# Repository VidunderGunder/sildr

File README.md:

# Sildr

Everything Sildr and technical.

1.0 and 2.0 are legacy, and some relevant documentation can be found in `/legacy`. Keep in mind it's mostly in Norwegian.

## Order History

**Components:**  
https://no.mouser.com/OrderHistory/OrdersView.aspx  
Email: kristiankramas@outlook.com  
Username: `vidundergunder`  
Password: `******`

**PCB:**  
https://jlcpcb.com/order#EL  
Email: kristiankramas@outlook.com  
Username: `vidundergunder`  
Password: `******`

## Electrical System v3.0

### Overview Illustration (click on image to open Figma):

The system is split in two parts:

1. Base system
2. Optional data logging system (requires the base system)

### Base System

#### Simplified circuit diagram (click on image to run simulation):

> _Image may be outdated_
> 
> - Behavior can be controlled with an MCU, and has an analog fallback
> - Relay represents the solenoid valve
> - Voltmeter is a digital in pin, registering 0V as button presses
> - Logic sources are digital out pins
> - Resistor connected to pin 7 and 6 on the 555-timer can be changed out for a potentiometer to manually set timer on-site

#### Simulated Prototype Circuit (click on image to run simulation):

> _Image may be outdated_  
> 
> - Simulation requires an Autodesk account (you can use your google account)
> - Lightbulb represents the solenoid valve

#### Prototype Components

- 1x 555-timer
- 3x nMOS Transistor (MOSFET)  
(FQP30N06L 60V LOGIC N-Channel MOSFET)
- 3x 1k resistor
- 1x 4k7 resistor
- 1x 330 resistor
- 1x 1mF capacitor
- 1x Pushbutton
- 1x diode
- 12V DC power supply
- 5V DC power supply

#### Production Components

| Component      | Description                   | Image                                                    |
| -------------- | ----------------------------- | -------------------------------------------------------- |
| Button         | [Schurter Touchless Switch TTS](https://www.schurter.com/en/datasheet/TTS) |  |
| Solenoid Coil (Valve) | [Danfoss BE012DS Coil](https://store.danfoss.com/no/no/Climate-Solutions-for-cooling/Ventiler/Ventilspoler/Spoler-for-Magnetventiler/Magnetventilspole%2C-BE012DS%2C-Koblingsboks%2C-Multipakk/p/018F6756#/) |  |
| Transformer | [230VAC to 12VDC 2.0A (NB: Pick correct option)](https://www.biltema.no/en-no/construction/electrical-installations/lamp-sockets/led-transformer-12-v-dc-2000038013) |  |

### Data Logging System (optional)

_TODO_

| Component      | Description                   | Image                                                    |
| -------------- | ----------------------------- | -------------------------------------------------------- |
| Flowmeter | [Sensus HRI Pulsgiver](https://www.ahlsell.no/products/vvs-teknisk-produkter/ventiler---filter-og-instrumenter/vannmalere-med-tilbehor/4021402/) (1pulse/liter) [Datasheet](https://nobb-vavvs.no/API/Produktfiler/LastNed?id=27486&inline=) |  |

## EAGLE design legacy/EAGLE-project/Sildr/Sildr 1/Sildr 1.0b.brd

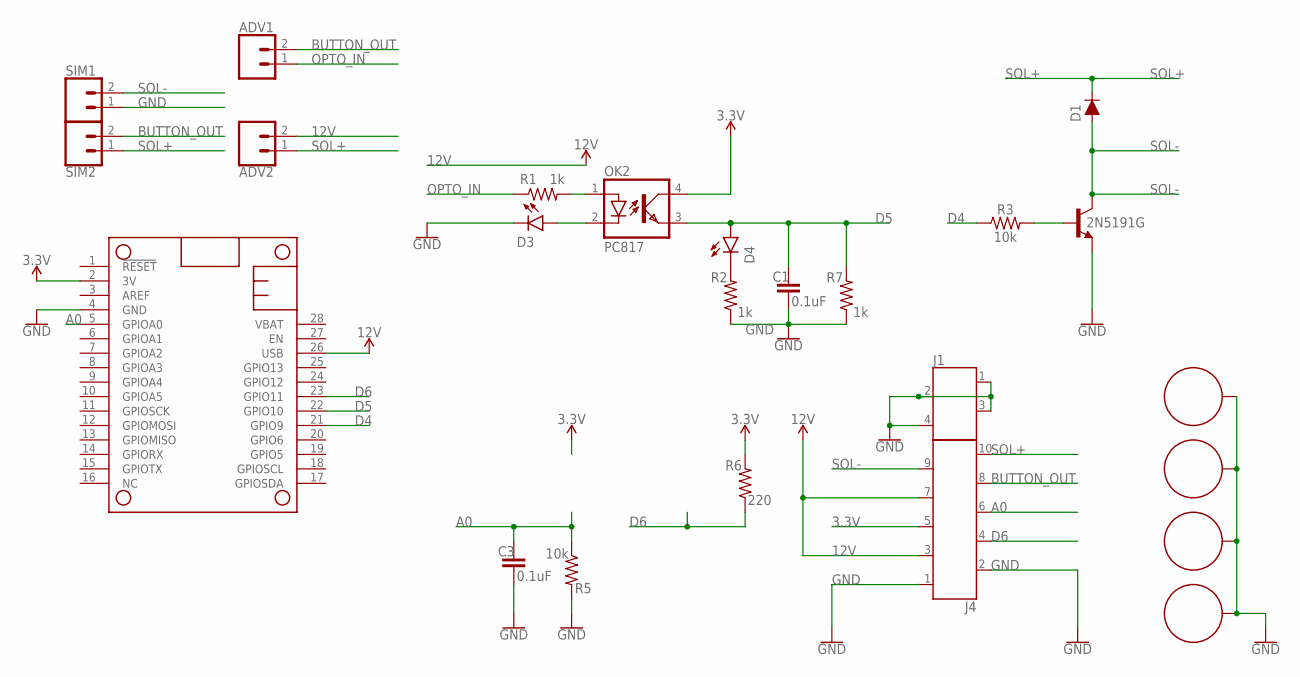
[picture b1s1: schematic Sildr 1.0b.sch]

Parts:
2N5191G: 2SC1944; T-30_V
ADV1, ADV2: CONN_02; 1X02
C1, C3: 0.1uF; CAP-PTH-SMALL-KIT
D1: 1A/50V/1.1V; DIODE-1N4001
D3, D4: LED3MM; LED_3MM
H1, H2, H3, H6: STANDOFF_ELECTRICAL; STANDOFF-ELECTRICAL
J1: 691412320004
J4: 691412320010
MS1: FEATHERWING_NODIM; FEATHERWING_DIM
OK2: PC817; DIL04
R1, R2, R7: 1k; AXIAL-0.3
R3, R5: 10k; AXIAL-0.3
R6: 220; AXIAL-0.3
SIM1, SIM2: CONN_02; 1X02

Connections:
3.3V: J4.5, MS1.2 (3V), OK2.4 (COL), R6.P$2 (2)
12V: ADV2.2, J4.3, J4.7, MS1.26 (USB)
A0: C3.1, J4.6, MS1.5 (GPIOA0), R5.P$1 (1)
BUTTON_OUT: ADV1.2, J4.8, SIM2.2
D4: MS1.21 (GPIO9), R3.P$1 (1)
D5: C1.1, D4.A, MS1.22 (GPIO10), OK2.3 (EMIT), R7.P$2 (2)
D6: J4.4, MS1.23 (GPIO11), R6.P$1 (1)
GND: 2N5191G.3 (E), C1.2, C3.2, D3.K (C), H1.P1, H2.P1, H3.P1, H6.P1, J1.1, J1.2, J1.3, J1.4, J4.1, J4.2, MS1.4 (GND), R2.P$1 (1), R5.P$2 (2), R7.P$1 (1), SIM1.1
unnamed: 2N5191G.1 (B), R3.P$2 (2)
unnamed: D3.A, OK2.2 (C)
unnamed: OK2.1 (A), R1.P$2 (2)
unnamed: D4.K (C), R2.P$2 (2)
OPTO_IN: ADV1.1, R1.P$1 (1)
SOL+: ADV2.1, D1.C, J4.10, SIM2.1
SOL-: 2N5191G.2 (C), D1.A, J4.9, SIM1.2

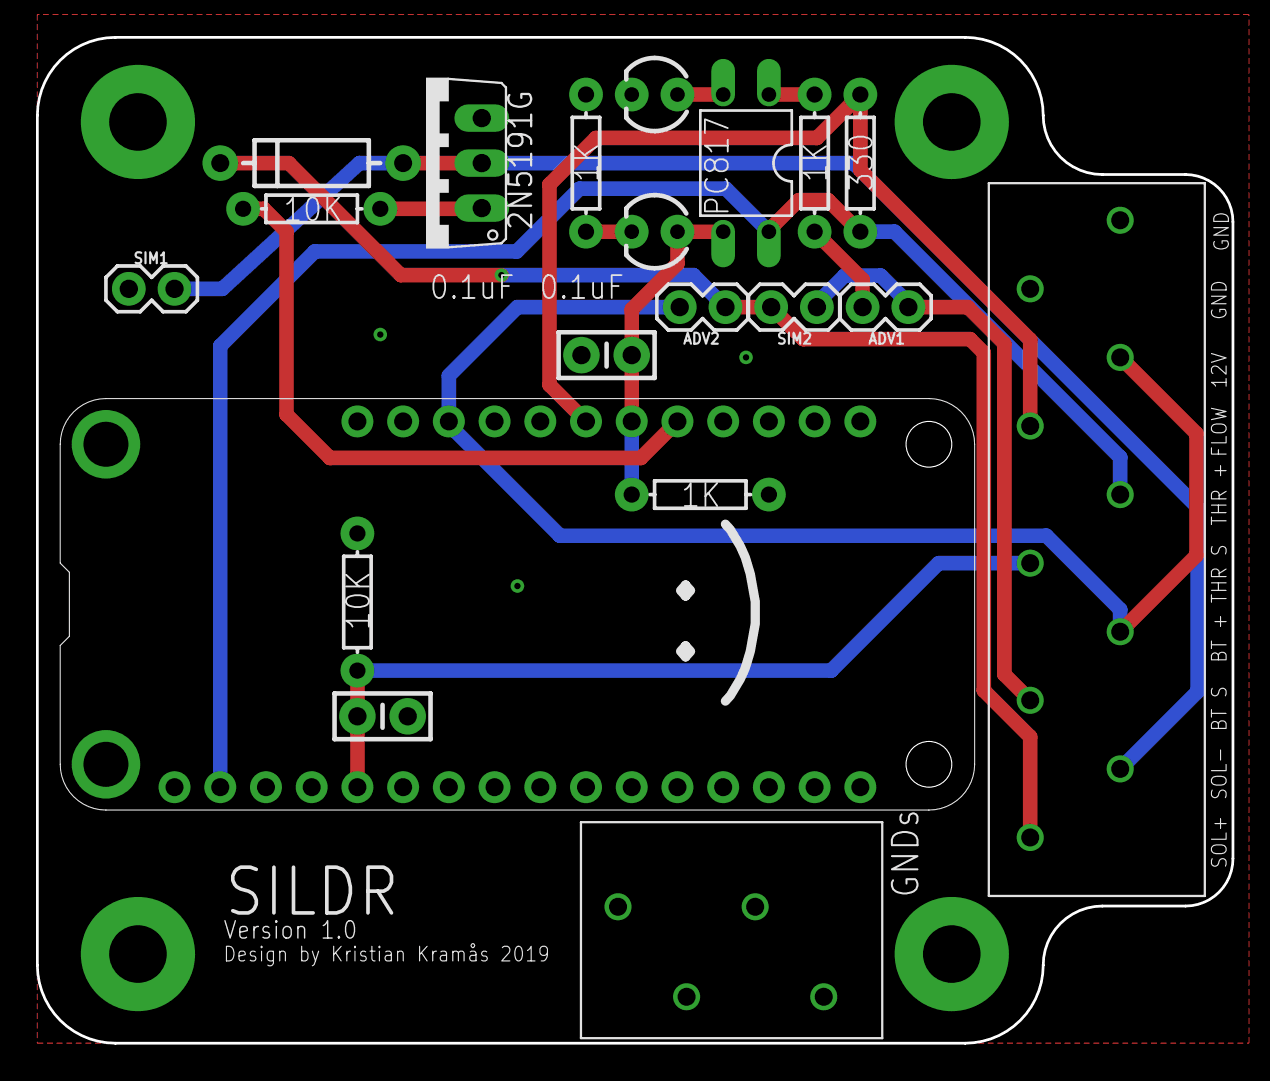
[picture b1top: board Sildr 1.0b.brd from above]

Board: 2 copper layers, 66.4 x 55.9 mm, 24 parts (0 on the bottom side), 15 nets.

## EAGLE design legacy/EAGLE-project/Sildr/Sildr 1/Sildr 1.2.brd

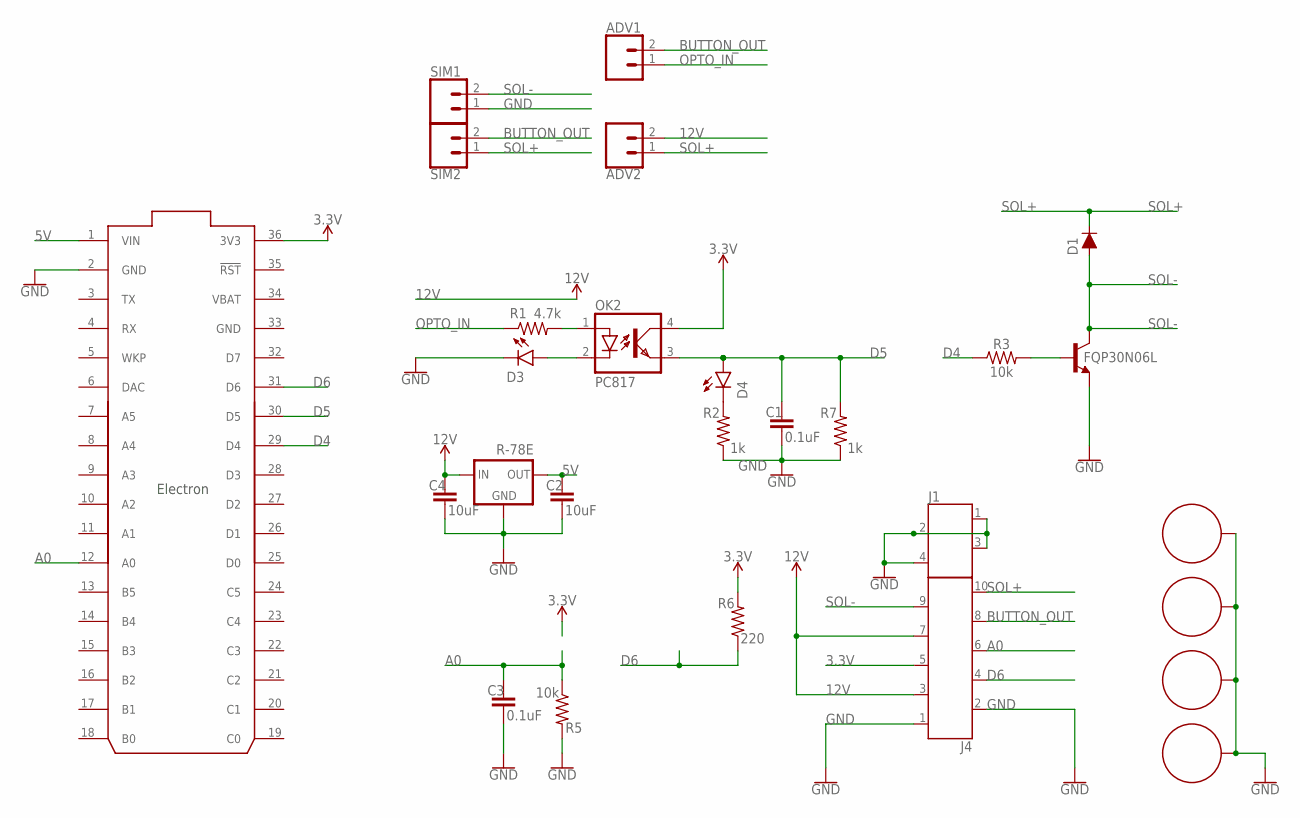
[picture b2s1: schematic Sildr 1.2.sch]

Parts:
ADV1, ADV2: CONN_02; 1X02
C1, C3: 0.1uF; CAP-PTH-SMALL-KIT
C2, C4: 10uF; CAP-PTH-SMALL-KIT
D1: 1A/50V/1.1V; DIODE-1N4001
D3, D4: LED3MM; LED_3MM
FQP30N06L: 2SC1944; T-30_V
H1, H2, H3, H6: STANDOFF_ELECTRICAL; STANDOFF-ELECTRICAL
J1: 691412320004
J4: 691412320010
OK2: PC817; DIL04
R1: 4.7k; AXIAL-0.3
R2, R7: 1k; AXIAL-0.3
R3, R5: 10k; AXIAL-0.3
R6: 220; AXIAL-0.3
R-78E: R-78E5.0-1.0; DC-DC_CONVERTER_78XX
SIM1, SIM2: CONN_02; 1X02
U$1: ELECTRON_WITH_HEADERS; ELECTRON

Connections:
3.3V: J4.5, OK2.4 (COL), R6.P$2 (2), U$1.36 (3V3)
5V: C2.1, R-78E.VOUT (OUT), U$1.1 (VIN)
12V: ADV2.2, C4.1, J4.3, J4.7, R-78E.VIN (IN)
A0: C3.1, J4.6, R5.P$1 (1), U$1.12 (A0)
BUTTON_OUT: ADV1.2, J4.8, SIM2.2
D4: R3.P$1 (1), U$1.29 (D4)
D5: C1.1, D4.A, OK2.3 (EMIT), R7.P$2 (2), U$1.30 (D5)
D6: J4.4, R6.P$1 (1), U$1.31 (D6)
GND: C1.2, C2.2, C3.2, C4.2, D3.K (C), FQP30N06L.3 (E), H1.P1, H2.P1, H3.P1, H6.P1, J1.1, J1.2, J1.3, J1.4, J4.1, J4.2, R2.P$1 (1), R5.P$2 (2), R7.P$1 (1), R-78E.GND, SIM1.1, U$1.2 (GND), U$1.33 (GND)
unnamed: FQP30N06L.1 (B), R3.P$2 (2)
unnamed: D3.A, OK2.2 (C)
unnamed: OK2.1 (A), R1.P$2 (2)
unnamed: D4.K (C), R2.P$2 (2)
OPTO_IN: ADV1.1, R1.P$1 (1)
SOL+: ADV2.1, D1.C, J4.10, SIM2.1
SOL-: D1.A, FQP30N06L.2 (C), J4.9, SIM1.2
VBAT: U$1.34 (VBAT)

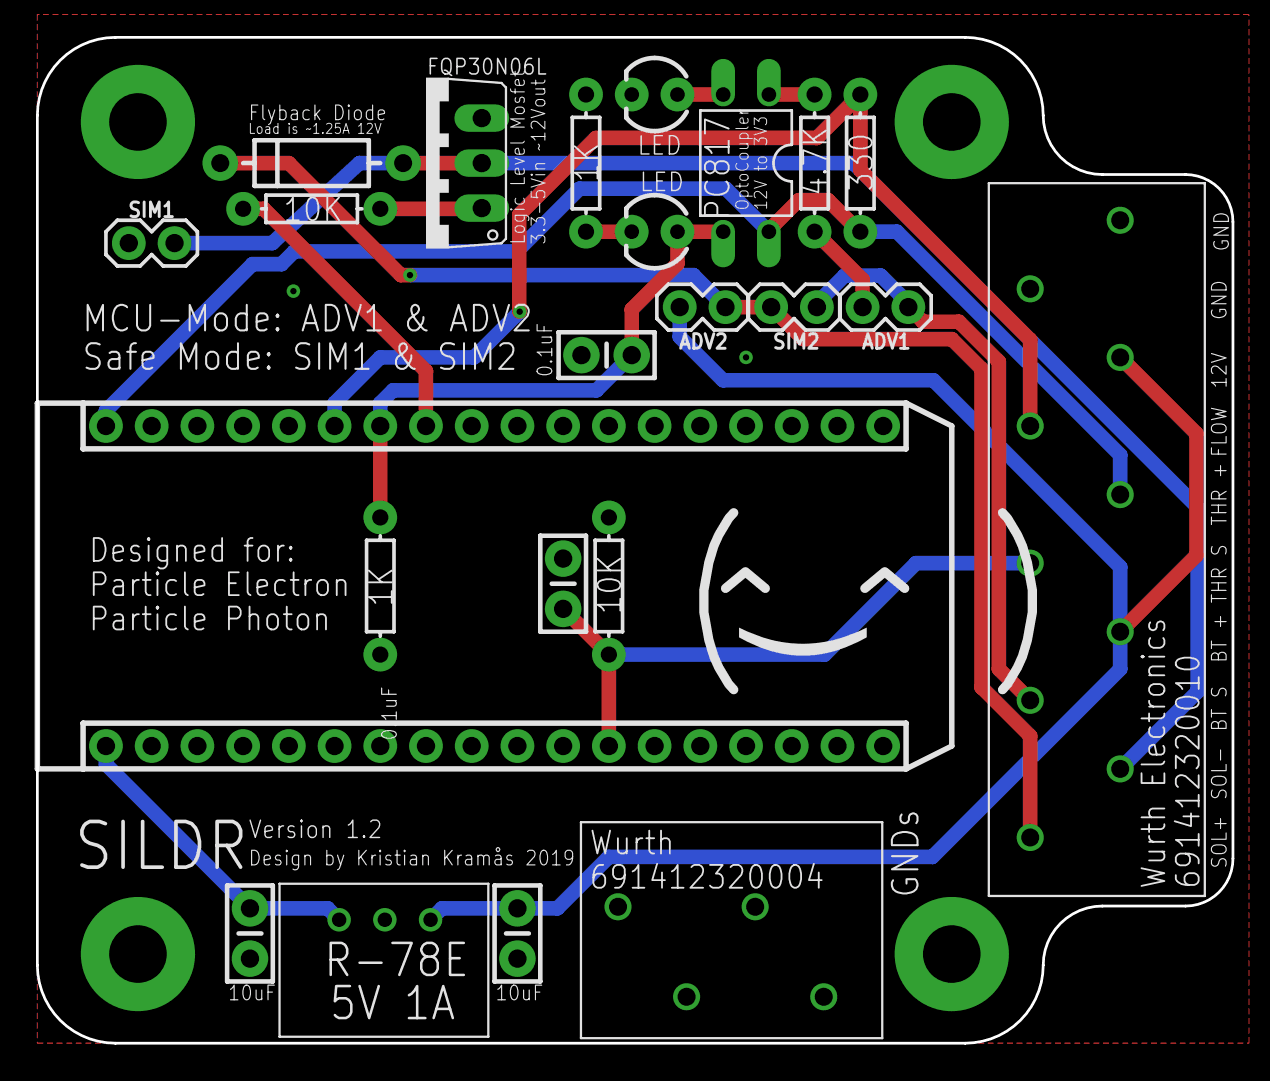
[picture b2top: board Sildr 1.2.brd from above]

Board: 2 copper layers, 66.4 x 55.9 mm, 27 parts (0 on the bottom side), 16 nets.

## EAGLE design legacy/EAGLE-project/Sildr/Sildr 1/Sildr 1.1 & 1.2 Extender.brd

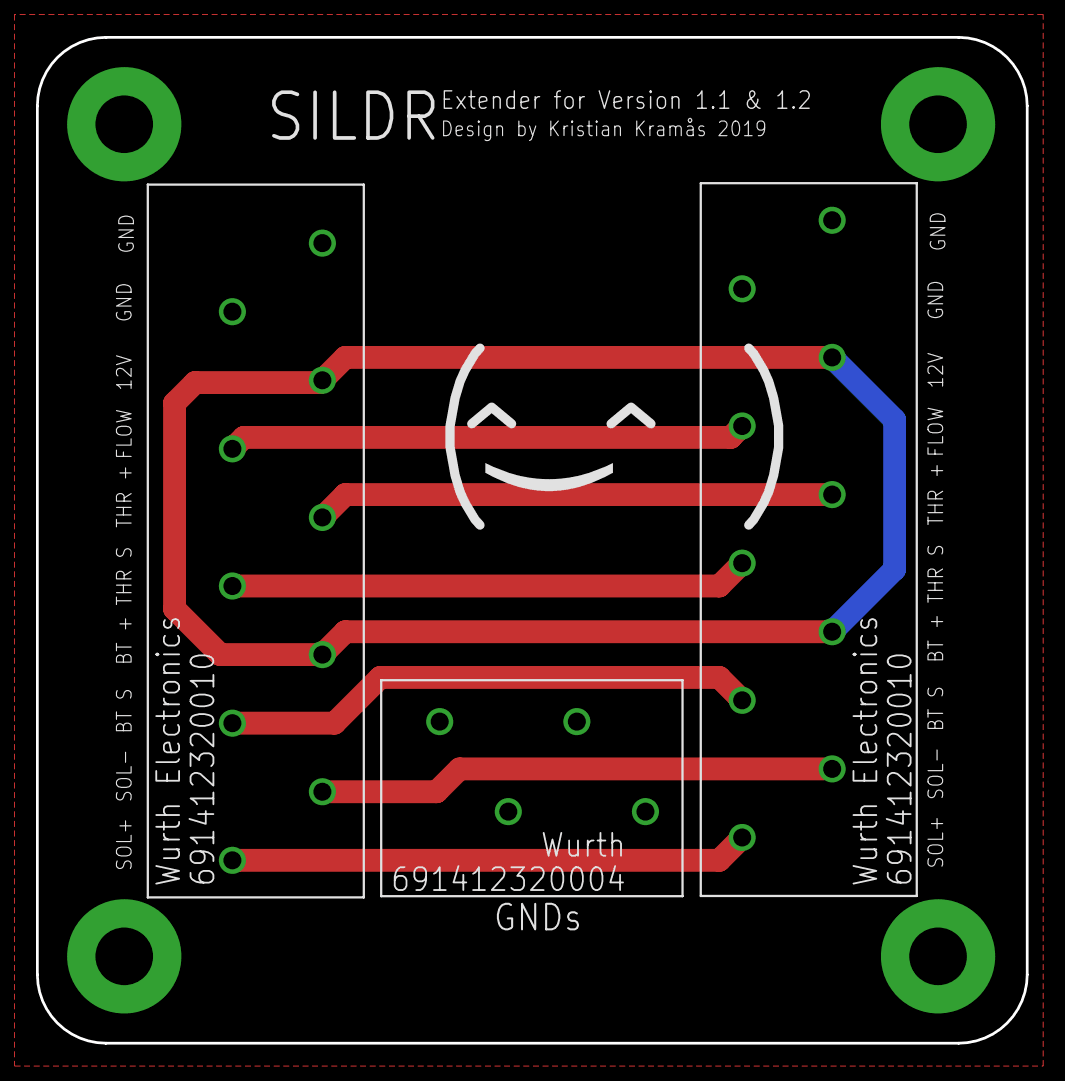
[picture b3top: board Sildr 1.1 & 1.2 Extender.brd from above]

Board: 2 copper layers, 55.0 x 55.9 mm, 7 parts (0 on the bottom side), 8 nets.

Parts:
H1, H2, H3, H6: STANDOFF_ELECTRICAL; STANDOFF-ELECTRICAL
J1: 691412320004
J2, J4: 691412320010

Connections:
3.3V: J2.6, J4.5
12V: J2.4, J2.8, J4.3, J4.7
A0: J2.5, J4.6
BUTTON_OUT: J2.3, J4.8
D6: J2.7, J4.4
GND: H1.P1, H2.P1, H3.P1, H6.P1, J1.1, J1.2, J1.3, J1.4, J2.9, J2.10, J4.1, J4.2
SOL+: J2.1, J4.10
SOL-: J2.2, J4.9

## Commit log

2021-10-25 init
2021-11-03 Added Schurter TTS buttons
2022-04-04 Misc
2022-07-02 Legacy docs and new circuit
2022-07-02 Updated circuit
2022-07-02 Safer logic sources
2022-07-03 4k7 to 1k resistor to simplify BOM
2022-07-03 Circuit Details
2022-07-03 Prototype Circuit ++
2022-07-03 Fixed headers formatting
2022-07-03 Readme tweaks
2022-07-03 Explained lightbulb
2022-07-03 Formatting
2022-07-03 Prototype image during sim

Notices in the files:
parts and their libraries:
SparkFun-Capacitors: Licensing: Creative Commons ShareAlike 4.0 International - https://creativecommons.org/licenses/by-sa/4.0
TerminalBlocks: Copyright: Würth Elektronik
Particle-Devices: Licensing: Designed by Particle.
